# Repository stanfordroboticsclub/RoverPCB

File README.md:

# RoverPCB
Collection of KiCad PCB projects for the rover

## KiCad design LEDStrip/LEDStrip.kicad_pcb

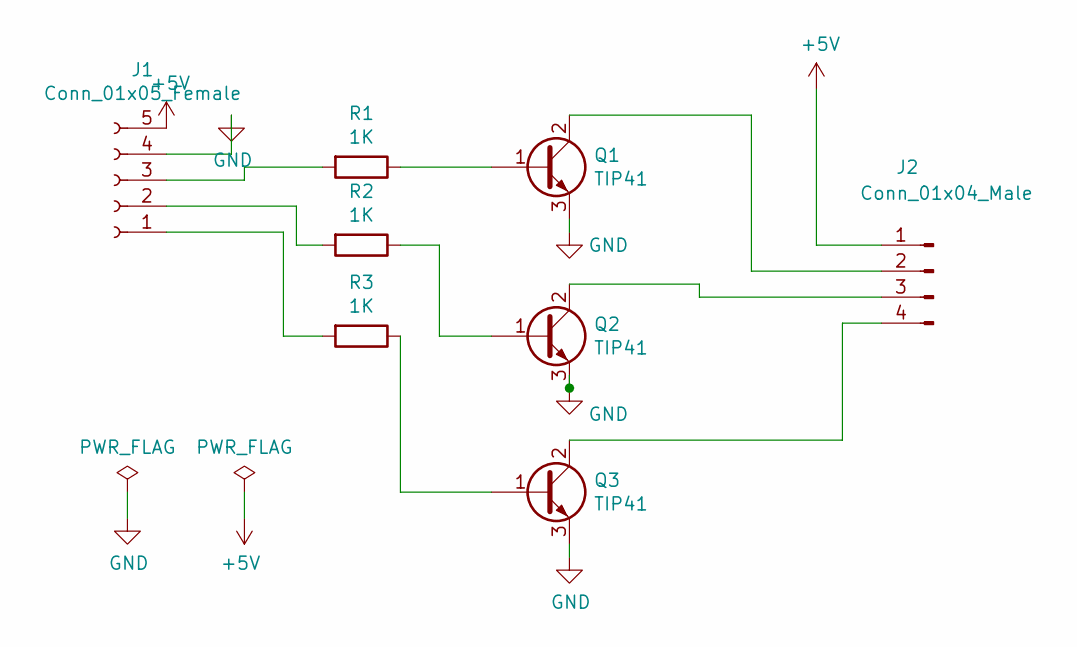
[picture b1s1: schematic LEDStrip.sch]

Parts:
J1: Conn_01x05_Female; PinHeader_1x05_P2.54mm_Vertical
J2: Conn_01x04_Male; PinHeader_1x04_P2.54mm_Vertical
Q1, Q2, Q3: TIP41; TO-220-3_Vertical
R1, R2, R3: 1K; R_2010_5025Metric_Pad1.52x2.65mm_HandSolder

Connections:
+5V: J1.5, J2.1
GND: J1.4, Q1.3 (E), Q2.3 (E), Q3.3 (E)
unnamed: J1.1, R3.2
unnamed: J1.2, R2.2
unnamed: J1.3, R1.2
unnamed: J2.2, Q1.2 (C)
unnamed: J2.3, Q2.2 (C)
unnamed: J2.4, Q3.2 (C)
unnamed: Q1.1 (B), R1.1
unnamed: Q2.1 (B), R2.1
unnamed: Q3.1 (B), R3.1

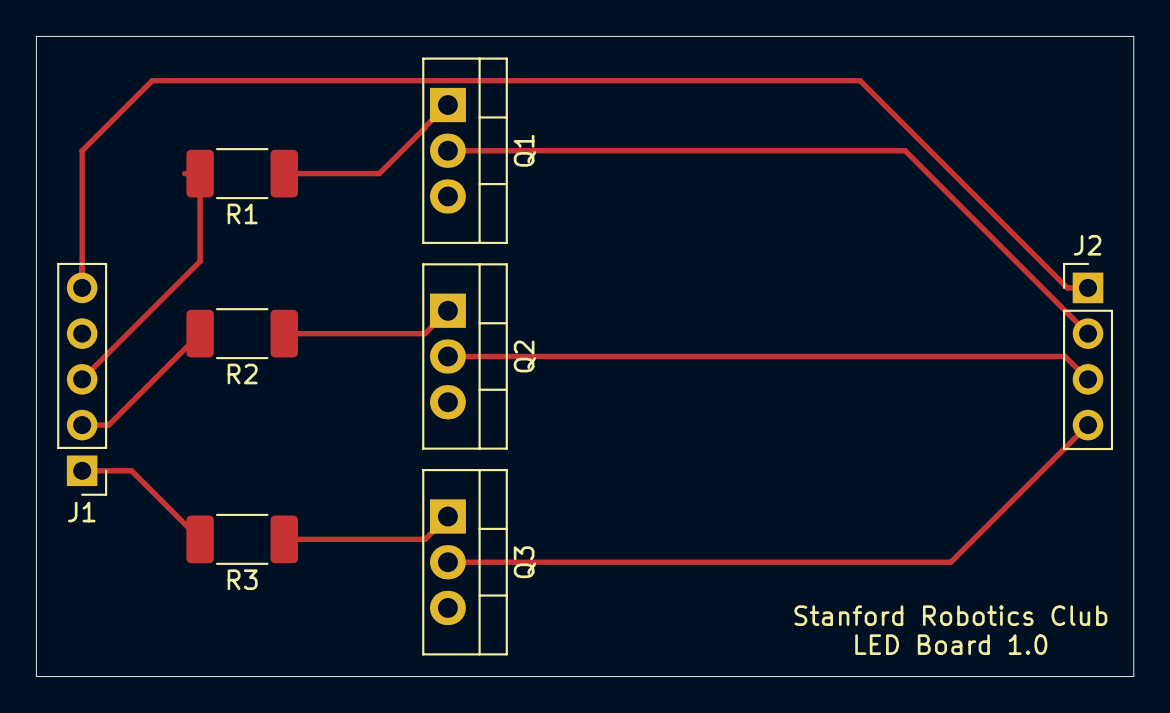
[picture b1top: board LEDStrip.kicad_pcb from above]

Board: 2 copper layers, 61.0 x 35.6 mm, 8 parts (0 on the bottom side), 11 nets.

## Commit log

2020-01-25 Add files via upload (#1)
2020-01-25 Add files via upload
    Diptrace Files (schematics + gerber) for the hall sensor board
